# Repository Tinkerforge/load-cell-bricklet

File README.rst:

Load Cell Bricklet
==================

This repository contains the firmware source code and the hardware design
files. The documentation generator configs can be found at
https://github.com/Tinkerforge/generators

Repository Content
------------------

software/:
 * examples/: Examples for all supported languages
 * build/: Compiled files
 * src/: Source code of firmware
 * Makefile: Makefile to build project

hardware/:
 * Contains KiCad project files and additionally schematics as PDF

datasheets/:
 * Contains datasheets for sensors and complex ICs that are used

Hardware
--------

The hardware is designed with the open source EDA Suite KiCad
(http://www.kicad.org). Before you are able to open the files,
you have to install the Tinkerforge kicad-libraries
(https://github.com/Tinkerforge/kicad-libraries). You can either clone
them directly in hardware/ or clone them in a separate folder and
symlink them into hardware/
(ln -s kicad_path/kicad-libraries project_path/hardware). After that you
can open the .pro file in hardware/ with KiCad and from there view and
modify the schematics and the PCB layout.

Software
--------

If you want to do your own Brick/Bricklet firmware development we highly
recommend that you use our build environment setup script and read the
tutorial (https://www.tinkerforge.com/en/doc/Tutorials/Tutorial_Build_Environment/Tutorial.html).

To compile the C code we recommend you to install the newest GNU Arm Embedded
Toolchain (https://launchpad.net/gcc-arm-embedded/+download).
You also need to install bricklib (https://github.com/Tinkerforge/bricklib)
and brickletlib (https://github.com/Tinkerforge/brickletlib).

You can either clone it directly in software/src/ or clone it in a
separate folder and symlink it into software/src/
(ln -s bricklib_path/bricklib project_path/software/src/ and
ln -s brickletlib_path/brickletlib project_path/software/src/).
Finally make sure to have CMake installed
(http://www.cmake.org/cmake/resources/software.html).

After that you can build the firmware by invoking make in software/.
The firmware (.bin) can then be found in software/build/ and uploaded
with brickv (click button "Flashing" on start screen).

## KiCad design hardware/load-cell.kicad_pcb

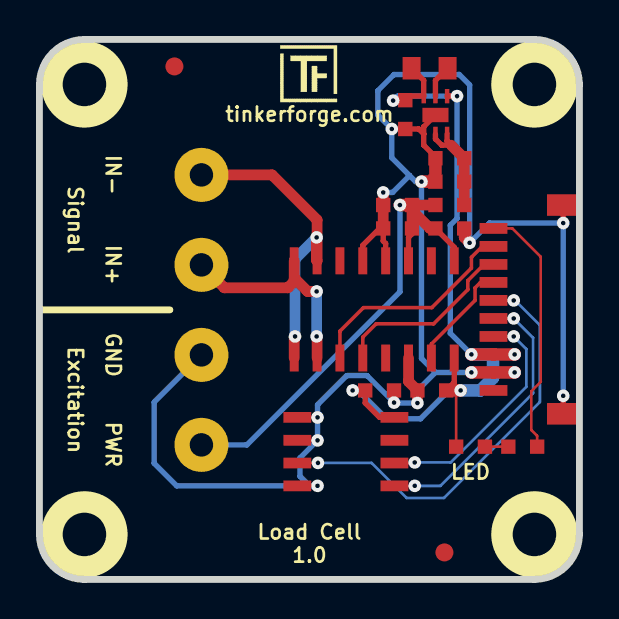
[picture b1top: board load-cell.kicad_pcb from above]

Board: 2 copper layers, 30.0 x 30.0 mm, 25 parts (0 on the bottom side), 15 nets.

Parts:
C1: 2.2µF; C0603
C2, C4, C5, C6, C7: 100nF; C0603
C3: 4.7µF; C0603
C8: 1µF; C0603
D1: LED; D0603
Fiducial_Mark: VAL**; Fiducial_Mark
Fiducial_Mark#2: VAL**; Fiducial_Mark
L1: 1µH; C0805
L2: FB0603-2; C0603
P1: CON-SENSOR
P2, P3: AKL_5_2
R1: 1k; R0603
U1: M24C64; SOIC8
U2: FAN4860; UMLP_22
U3: HX711; SOP16L
U4, U5, U6, U7: DRILL; DRILL_NP
VAL: CE_5mm

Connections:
3V3: C1.2, C2.1, C6.2, D1.2, L1.2, P1.3, U1.8, U2.4, U2.6, U3.16
+5V: C3.2, C4.1, L2.2, U2.2, U2.3
+5VA: C5.2, C7.1, C8.1, L2.1, P3.1, U3.1, U3.3
AGND: C1.1, C2.2, C3.1, C4.2, C5.1, C6.1, C7.2, C8.2, P1.2, P1.EP, P3.2, U1.1, U1.2, U1.4, U2.1, U2.EP, U3.4, U3.5, U3.14
unnamed: D1.1, R1.1
unnamed: L1.1, U2.5
unnamed: P1.6, U1.3
unnamed: P1.7, U3.15
unnamed: P1.8, U3.12
unnamed: P1.9, U3.11
unnamed: P1.10, R1.2
unnamed: P2.1, U3.8, U3.10
unnamed: P2.2, U3.7, U3.9
SCL: P1.4, U1.6
SDA: P1.5, U1.5

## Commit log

2015-03-05 Add stub implementation of Load Cell Bricklet API
2015-03-23 Implement Load Cell Bricklet API
2015-03-26 add hardware files for load cell bricklet
2015-03-26 add schematic
2015-03-31 add 5v boost regulator, routing not finished
2015-04-01 routing finished
2015-04-02 add fiducials
2015-04-02 change port description, fix routing
2015-04-16 Add .gitignore
2015-04-16 Change pin configuration to production version
2015-04-17 update schematic to current version
2015-04-17 Allow for a negative weight.
2015-04-24 drc executed
2015-04-29 Make sure to never divide by zero
2015-04-29 Add Python examples
2015-04-30 Make sure every setter returns a message if necessary
2015-04-30 Add tare function to Load Cell API
2015-05-05 Add hx711 datasheet
2015-05-05 Handle negative ADC values
2015-05-05 Handle divisor and dividend = 0 correclty
2015-05-06 Add C examples
2015-05-06 Use int32_t for weight
2015-05-06 Add C# examples
2015-05-06 Add Delphi examples
2015-05-06 Add Java examples
2015-05-06 Add JavaScript examples
2015-05-06 Add Perl examples
2015-05-06 Add PHP examples
2015-05-06 Add Ruby examples
2015-05-06 Add Shell examples
2015-05-06 Add VB.NET examples
2015-05-06 Add matlab/octave examples
2015-05-06 Add Mathematica examples
2015-05-08 last_value should only be set in bricklet_simple
2015-05-11 fix weee footprint
2015-06-19 Add LabVIEW and Mathematica examples
    Also clean up other examples.
2015-07-16 Add load cell drawings
2015-07-25 Make JavaScript browser example textarea readonly
2015-07-27 Cleanup C/C++, C#, Java, Python and Ruby examples
2015-07-29 Reformat changelog
2015-08-07 Use full device class name in Python examples
2015-08-12 Fix minor warnings in C/C++ examples
2015-08-14 Cleanup Delphi examples
2015-08-18 Cleanup VB.NET examples
2015-08-19 Cleanup Perl examples
2015-09-09 Duplicate cmake call to fix bug during cmake creation
2015-10-21 Generator based example cleanup
2015-11-04 Fix inversion in weight calculation
2015-11-12 Use g instead of kg to simplify example generation
2015-11-12 matlab: Fix callback handling for R2014a
    http://undocumentedmatlab.com/blog/matlab-callbacks-for-java-events-in-r2014a
2015-11-25 Include date and commit into changelog
2016-05-18 c: Add missing device destroy call
2016-07-01 Make the change UID comment more explicit
2017-04-13 csharp: Adapt example
2017-04-21 shell: Adapt example
2017-06-02 octave: Use javaObject instead of deprecated java_new
2017-08-04 Add 3d information (final); fix orientation of symbols
2017-08-04 Add 3d model (*.step & *.FCStd)
2017-11-30 Update examples from generator
2017-12-07 mathematica: Also generate .nb files
2018-02-02 Update examples
2018-02-19 javascript: Close div tag correctly
2018-02-20 Cleanup KiCad libraries config
    Ensure LibDir=kicad-libraries and LibName1=tinkerforge.
    Remove special library.
2018-05-24 perl: Use strict in examples
2018-07-11 Add Makefile with docker support
2018-07-11 Update directory structure and build instructions
2018-07-11 Remove obsolete generate_makefile scripts
2018-11-06 Add rust examples
2018-11-07 rust: Accept host names for ip connection, fix naming inconsistencies
2018-11-07 rust: Rename callback receivers.
2018-12-14 Add go examples.
2018-12-18 go: Change import path.
2018-12-18 go: Change import path again.
2018-12-20 rust: Reformat examples.
2019-01-24 mqtt: Add examples.
2019-01-24 mqtt: Fix example header.
2019-01-24 mqtt: Remove executable bit in example permissions.
2019-01-24 go: Minor example fixes.
2019-01-24 mqtt: Minor example fixes.
2019-03-28 mqtt: Fix whitespace.
2019-08-22 c: Adapt to bindings changes
2020-01-13 examples: Use python3 input instead of python2 raw_input.
2020-01-13 examples: mqtt: Remove trailing whitespace.
2020-04-14 mqtt: Fix device name format
2021-10-25 Update KiCad link
    https://www.kicad.org/blog/2021/10/Avoid-links-to-former-kicad-domain/
2022-05-10 go: Fix format string
2022-07-06 Add license files.

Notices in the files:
hardware/load-cell.kicad_pcb:
Licensed under CERN OHL v.1.1
Copyright (©) 2015, B.Nordmeyer
Copyright Tinkerforge GmbH 2015.
This documentation describes Open Hardware and is licensed under the
CERN OHL v. 1.1.
